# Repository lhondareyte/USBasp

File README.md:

## USBasp firmware
Latest version of USBasp firmware with TPI support and Green Photon hack for chinese ISP programmers based on ATmega8/48/88.

See [Thomas Fischl's website](https://www.fischl.de/usbasp/) and [Green Photons's blog](https://www.sciencetronics.com/greenphotons/?p=1937) for details.

### Build
Make sure you have avr-gcc toolchain installed. To build the patched version, just type:

`make main.hex`

To build original version, just type:

`make -f Makefile.genuine main.hex`

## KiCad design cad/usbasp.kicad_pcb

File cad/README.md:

## USBasp schematics with 3v3 support

* [See here for details](http://lhondareyte.free.fr/wordpress/?p=2791).
* [Thomas Fischl's original schematic](https://www.fischl.de/usbasp/).

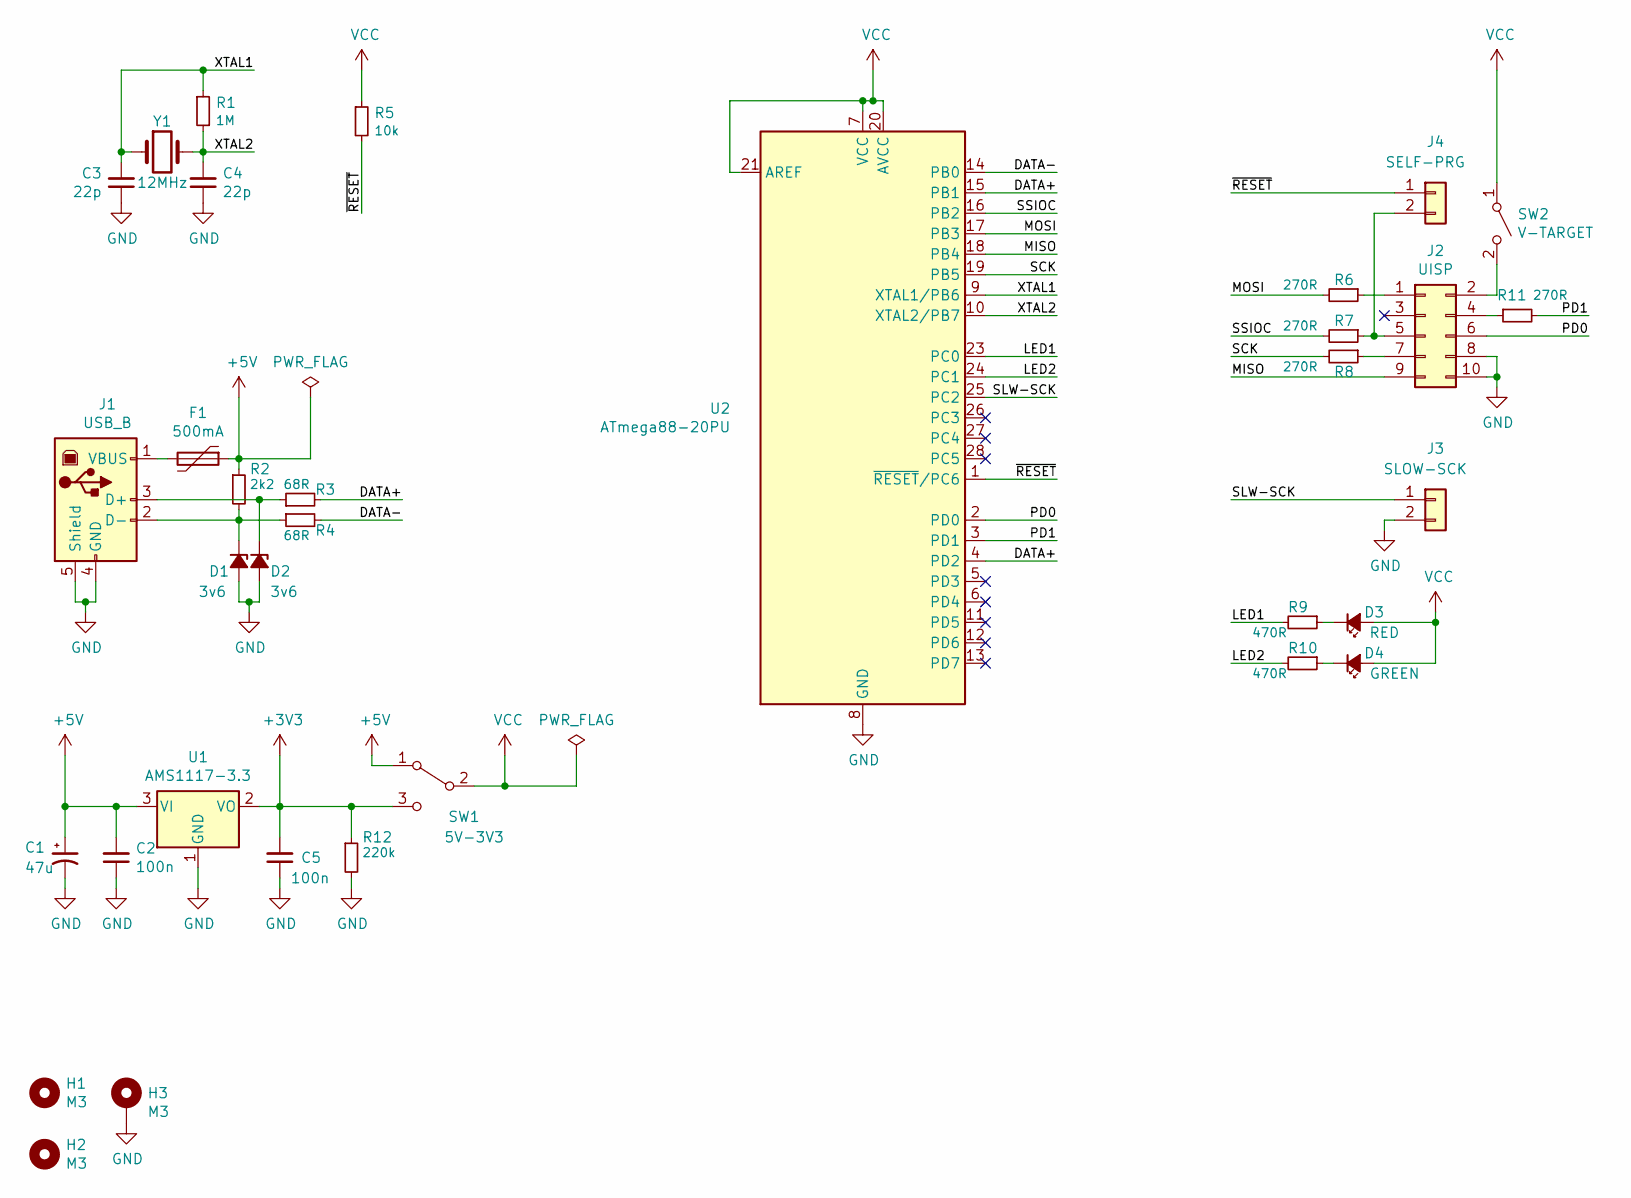
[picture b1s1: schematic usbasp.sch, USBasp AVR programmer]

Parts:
C1: 47u; CP_Radial_D5.0mm_P2.50mm
C2, C5: 100n; C_1206_3216Metric_Pad1.42x1.75mm_HandSolder
C3, C4: 22p; C_1206_3216Metric_Pad1.42x1.75mm_HandSolder
D1, D2: 3v6; D_1206_3216Metric_Pad1.42x1.75mm_HandSolder
D3: RED; LED_D3.0mm_FlatTop
D4: GREEN; LED_D3.0mm_FlatTop
F1: 500mA; D_1206_3216Metric_Pad1.42x1.75mm_HandSolder
H1, H2: M3; MountingHole_3.2mm_M3
H3: M3; MountingHole_3.2mm_M3_Pad
J1: USB_B; USB_B_OST_USB-B1HSxx_Horizontal
J2: UISP; PinHeader_2x05_P2.54mm_Horizontal
J3: SLOW-SCK; PinHeader_1x02_P2.54mm_Vertical
J4: SELF-PRG; PinHeader_1x02_P2.54mm_Vertical
R1: 1M; R_1206_3216Metric_Pad1.42x1.75mm_HandSolder
R2: 2k2; R_1206_3216Metric_Pad1.42x1.75mm_HandSolder
R3, R4: 68R; R_1206_3216Metric_Pad1.42x1.75mm_HandSolder
R5: 10k; R_1206_3216Metric_Pad1.42x1.75mm_HandSolder
R6, R7, R8, R11: 270R; R_1206_3216Metric_Pad1.42x1.75mm_HandSolder
R9, R10: 470R; R_1206_3216Metric_Pad1.42x1.75mm_HandSolder
R12: 220k; R_1206_3216Metric_Pad1.42x1.75mm_HandSolder
SW1: 5V-3V3; PinHeader_1x03_P2.54mm_Vertical
SW2: V-TARGET; PinHeader_1x02_P2.54mm_Vertical
U1: AMS1117-3.3; SOT-223-3_TabPin2
U2: ATmega88-20PU; DIP-28_W7.62mm
Y1: 12MHz; Crystal_HC49-4H_Vertical

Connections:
+3V3: C5.2, R12.1, SW1.3 (C), U1.2 (VO)
+5V: C1.1, C2.2, F1.1, R2.1, SW1.1 (A), U1.3 (VI)
/DATA+: R3.2, U2.4 (PD2), U2.15 (PB1)
/DATA-: R4.2, U2.14 (PB0)
/LED1: R9.2, U2.23 (PC0)
/LED2: R10.2, U2.24 (PC1)
/MISO: J2.9, U2.18 (PB4)
/MOSI: R6.2, U2.17 (PB3)
/PD0: J2.6, U2.2 (PD0)
/PD1: R11.2, U2.3 (PD1)
/SCK: R8.2, U2.19 (PB5)
/SLW-SCK: J3.1, U2.25 (PC2)
/SSIOC: R7.2, U2.16 (PB2)
/XTAL1: C3.2, R1.1, U2.9 (XTAL1/PB6), Y1.1
/XTAL2: C4.2, R1.2, U2.10 (XTAL2/PB7), Y1.2
/~RESET: J4.1, R5.2, U2.1 (~RESET~/PC6)
GND: C1.2, C2.1, C3.1, C4.1, C5.1, D1.2 (A), D2.2 (A), H3.1, J1.4 (GND), J1.5 (Shield), J2.8, J2.10, J3.2, R12.2, U1.1 (GND), U2.8 (GND), U2.22 (GND)
unnamed: D1.1 (K), J1.2 (D-), R2.2, R4.1
unnamed: D2.1 (K), J1.3 (D+), R3.1
unnamed: D3.1 (K), R9.1
unnamed: D4.1 (K), R10.1
unnamed: F1.2, J1.1 (VBUS)
unnamed: J2.1, R6.1
unnamed: J2.2, SW2.2 (B)
unnamed: J2.4, R11.1
unnamed: J2.5, J4.2, R7.1
unnamed: J2.7, R8.1
VCC: D3.2 (A), D4.2 (A), R5.1, SW1.2 (B), SW2.1 (A), U2.7 (VCC), U2.20 (AVCC), U2.21 (AREF)

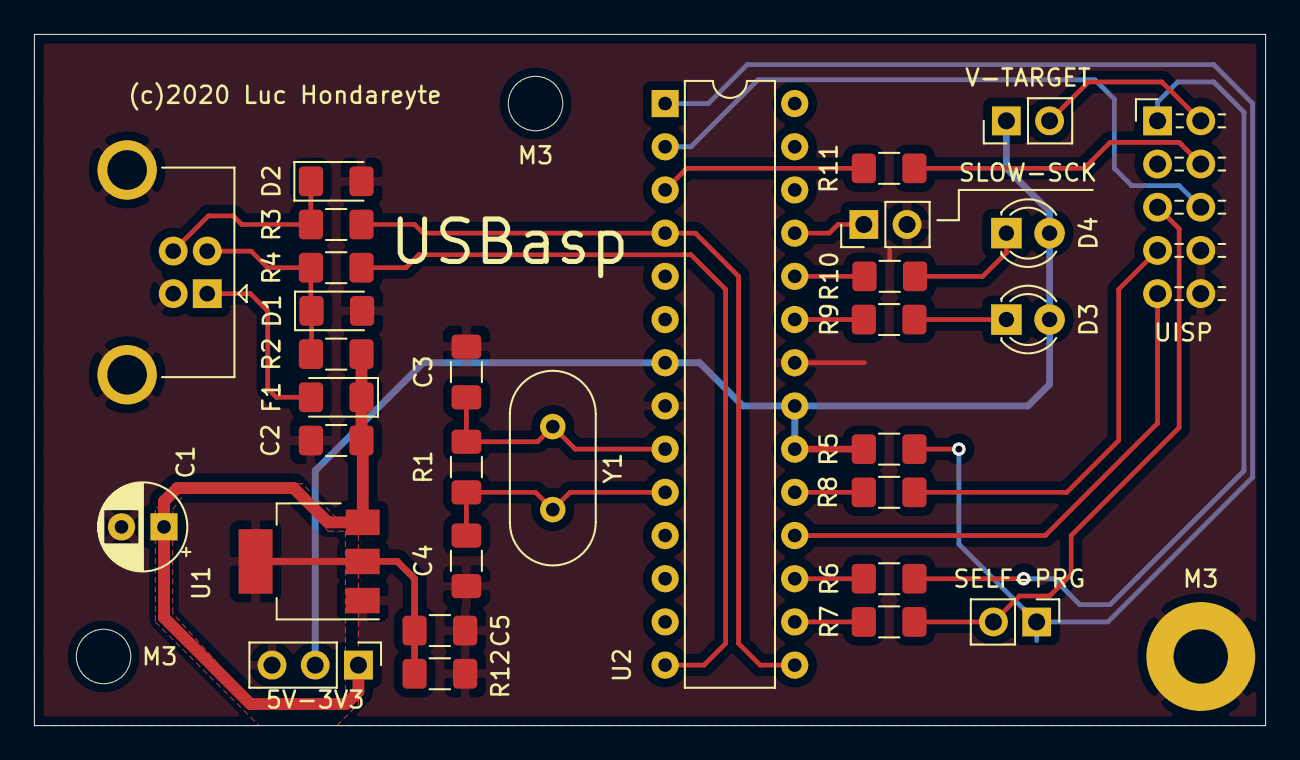
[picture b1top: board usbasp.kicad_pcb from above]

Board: 2 copper layers, 72.4 x 40.6 mm, 34 parts (0 on the bottom side), 28 nets.

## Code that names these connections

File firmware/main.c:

/*
 * USBasp - USB in-circuit programmer for Atmel AVR controllers
 *
 * Thomas Fischl <tfischl@gmx.de>
 *
 * License........: GNU GPL v2 (see Readme.txt)
 * Target.........: ATMega8 at 12 MHz
 * Creation Date..: 2005-02-20
 * Last change....: 2009-02-28
 *
 * PC2 SCK speed option.
 * GND  -> slow (8khz SCK),
 * open -> software set speed (default is 375kHz SCK)
 */

#include <avr/io.h>
#include <avr/interrupt.h>
#include <avr/pgmspace.h>
#include <avr/wdt.h>

#include "usbasp.h"
#include "usbdrv.h"
#include "isp.h"
#include "clock.h"
#include "tpi.h"
#include "tpi_defs.h"

static uchar replyBuffer[8];

static uchar prog_state = PROG_STATE_IDLE;
static uchar prog_sck = USBASP_ISP_SCK_AUTO;

static uchar prog_address_newmode = 0;
static unsigned long prog_address;
static unsigned int prog_nbytes = 0;
static unsigned int prog_pagesize;
static uchar prog_blockflags;
static uchar prog_pagecounter;

uchar usbFunctionSetup(uchar data[8]) {

	uchar len = 0;

	if (data[1] == USBASP_FUNC_CONNECT) {

		/* set SCK speed */
		if ((PINC & (1 << PC2)) == 0) {
			ispSetSCKOption(USBASP_ISP_SCK_8);
		} else {
			ispSetSCKOption(prog_sck);
		}

		/* set compatibility mode of address delivering */
		prog_address_newmode = 0;

		ledRedOn();
		ispConnect();

	} else if (data[1] == USBASP_FUNC_DISCONNECT) {
		ispDisconnect();
		ledRedOff();

	} else if (data[1] == USBASP_FUNC_TRANSMIT) {
		replyBuffer[0] = ispTransmit(data[2]);
		replyBuffer[1] = ispTransmit(data[3]);
		replyBuffer[2] = ispTransmit(data[4]);
		replyBuffer[3] = ispTransmit(data[5]);
		len = 4;

	} else if (data[1] == USBASP_FUNC_READFLASH) {

		if (!prog_address_newmode)
			prog_address = (data[3] << 8) | data[2];

		prog_nbytes = (data[7] << 8) | data[6];
		prog_state = PROG_STATE_READFLASH;
		len = 0xff; /* multiple in */

	} else if (data[1] == USBASP_FUNC_READEEPROM) {

		if (!prog_address_newmode)
			prog_address = (data[3] << 8) | data[2];

		prog_nbytes = (data[7] << 8) | data[6];
		prog_state = PROG_STATE_READEEPROM;
		len = 0xff; /* multiple in */

	} else if (data[1] == USBASP_FUNC_ENABLEPROG) {
		replyBuffer[0] = ispEnterProgrammingMode();
		len = 1;

	} else if (data[1] == USBASP_FUNC_WRITEFLASH) {

		if (!prog_address_newmode)
			prog_address = (data[3] << 8) | data[2];

		prog_pagesize = data[4];
		prog_blockflags = data[5] & 0x0F;
		prog_pagesize += (((unsigned int) data[5] & 0xF0) << 4);
		if (prog_blockflags & PROG_BLOCKFLAG_FIRST) {
			prog_pagecounter = prog_pagesize;
		}
		prog_nbytes = (data[7] << 8) | data[6];
		prog_state = PROG_STATE_WRITEFLASH;
		len = 0xff; /* multiple out */

	} else if (data[1] == USBASP_FUNC_WRITEEEPROM) {

		if (!prog_address_newmode)
			prog_address = (data[3] << 8) | data[2];

		prog_pagesize = 0;
		prog_blockflags = 0;
		prog_nbytes = (data[7] << 8) | data[6];
		prog_state = PROG_STATE_WRITEEEPROM;
		len = 0xff; /* multiple out */

	} else if (data[1] == USBASP_FUNC_SETLONGADDRESS) {

		/* set new mode of address delivering (ignore address delivered in commands) */
		prog_address_newmode = 1;
		/* set new address */
		prog_address = *((unsigned long*) &data[2]);

	} else if (data[1] == USBASP_FUNC_SETISPSCK) {

		/* set sck option */
		prog_sck = data[2];
		replyBuffer[0] = 0;
		len = 1;

	} else if (data[1] == USBASP_FUNC_TPI_CONNECT) {
		tpi_dly_cnt = data[2] | (data[3] << 8);

		/* RST high */
		ISP_OUT |= (1 << ISP_RST);
		ISP_DDR |= (1 << ISP_RST);

		clockWait(3);

		/* RST low */
		ISP_OUT &= ~(1 << ISP_RST);
		ledRedOn();

		clockWait(16);
		tpi_init();
	
	} else if (data[1] == USBASP_FUNC_TPI_DISCONNECT) {

		tpi_send_byte(TPI_OP_SSTCS(TPISR));
		tpi_send_byte(0);

		clockWait(10);

		/* pulse RST */
		ISP_OUT |= (1 << ISP_RST);
		clockWait(5);
		ISP_OUT &= ~(1 << ISP_RST);
		clockWait(5);

		/* set all ISP pins inputs */
		ISP_DDR &= ~((1 << ISP_RST) | (1 << ISP_SCK) | (1 << ISP_MOSI));
		/* switch pullups off */
		ISP_OUT &= ~((1 << ISP_RST) | (1 << ISP_SCK) | (1 << ISP_MOSI));

		ledRedOff();
	
	} else if (data[1] == USBASP_FUNC_TPI_RAWREAD) {
		replyBuffer[0] = tpi_recv_byte();
		len = 1;
	
	} else if (data[1] == USBASP_FUNC_TPI_RAWWRITE) {
		tpi_send_byte(data[2]);
	
	} else if (data[1] == USBASP_FUNC_TPI_READBLOCK) {
		prog_address = (data[3] << 8) | data[2];
		prog_nbytes = (data[7] << 8) | data[6];
		prog_state = PROG_STATE_TPI_READ;
		len = 0xff; /* multiple in */
	
	} else if (data[1] == USBASP_FUNC_TPI_WRITEBLOCK) {
		prog_address = (data[3] << 8) | data[2];
		prog_nbytes = (data[7] << 8) | data[6];
		prog_state = PROG_STATE_TPI_WRITE;
		len = 0xff; /* multiple out */
	
	} else if (data[1] == USBASP_FUNC_GETCAPABILITIES) {
		replyBuffer[0] = USBASP_CAP_0_TPI;
		replyBuffer[1] = 0;
		replyBuffer[2] = 0;
		replyBuffer[3] = 0;
		len = 4;
	}

	usbMsgPtr = replyBuffer;

	return len;
}

uchar usbFunctionRead(uchar *data, uchar len) {

	uchar i;

	/* check if programmer is in correct read state */
	if ((prog_state != PROG_STATE_READFLASH) && (prog_state
			!= PROG_STATE_READEEPROM) && (prog_state != PROG_STATE_TPI_READ)) {
		return 0xff;
	}

	/* fill packet TPI mode */
	if(prog_state == PROG_STATE_TPI_READ)
	{
		tpi_read_block(prog_address, data, len);
		prog_address += len;
		return len;
	}

	/* fill packet ISP mode */
	for (i = 0; i < len; i++) {
		if (prog_state == PROG_STATE_READFLASH) {
			data[i] = ispReadFlash(prog_address);
		} else {
			data[i] = ispReadEEPROM(prog_address);
		}
		prog_address++;
	}

	/* last packet? */
	if (len < 8) {
		prog_state = PROG_STATE_IDLE;
	}

	return len;
}

uchar usbFunctionWrite(uchar *data, uchar len) {

	uchar retVal = 0;
	uchar i;

	/* check if programmer is in correct write state */
	if ((prog_state != PROG_STATE_WRITEFLASH) && (prog_state
			!= PROG_STATE_WRITEEEPROM) && (prog_state != PROG_STATE_TPI_WRITE)) {
		return 0xff;
	}

	if (prog_state == PROG_STATE_TPI_WRITE)
	{
		tpi_write_block(prog_address, data, len);
		prog_address += len;
		prog_nbytes -= len;
		if(prog_nbytes <= 0)
		{
			prog_state = PROG_STATE_IDLE;
			return 1;
		}
		return 0;
	}

	for (i = 0; i < len; i++) {

		if (prog_state == PROG_STATE_WRITEFLASH) {
			/* Flash */

			if (prog_pagesize == 0) {
				/* not paged */
				ispWriteFlash(prog_address, data[i], 1);
			} else {
				/* paged */
				ispWriteFlash(prog_address, data[i], 0);
				prog_pagecounter--;
				if (prog_pagecounter == 0) {
					ispFlushPage(prog_address, data[i]);
					prog_pagecounter = prog_pagesize;
				}
			}

		} else {
			/* EEPROM */
			ispWriteEEPROM(prog_address, data[i]);
		}

		prog_nbytes--;

		if (prog_nbytes == 0) {
			prog_state = PROG_STATE_IDLE;
			if ((prog_blockflags & PROG_BLOCKFLAG_LAST) && (prog_pagecounter
					!= prog_pagesize)) {

				/* last block and page flush pending, so flush it now */
				ispFlushPage(prog_address, data[i]);
			}

			retVal = 1; // Need to return 1 when no more data is to be received
		}

		prog_address++;
	}

	return retVal;
}

int main(void) {
	uchar i, j;

	/* no pullups on USB and ISP pins */
	PORTD = 0;
	PORTB = 0;
#if defined (__GREEN_PHOTONS__)
	DDRD = 0x00;
#else
	/* all outputs except PD2 = INT0 */
	DDRD = ~(1 << 2);
#endif

	/* output SE0 for USB reset */
	DDRB = ~0;
	j = 0;
	/* USB Reset by device only required on Watchdog Reset */
	while (--j) {
		i = 0;
		/* delay >10ms for USB reset */
		while (--i)
			;
	}
	/* all USB and ISP pins inputs */
	DDRB = 0;

	/* all inputs except PC0, PC1 */
	DDRC = 0x03;
	PORTC = 0xfe;

	/* init timer */
	clockInit();

	/* main event loop */
	usbInit();
	sei();
	for (;;) {
		usbPoll();
	}
	return 0;
}

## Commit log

2018-02-11 Initial import.
2018-02-11 Add Green Photons workaround.
2018-02-11 Update README.md.
2020-05-09 Adding KiCad schematic.
2020-05-28 Schematic: add 3.3v support
2020-06-21 Add Makefile for genuine version
2020-06-27 cad: update USB connector 3D model.
2021-03-17 Update permissions

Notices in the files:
cad/usbasp.kicad_pcb:
(c)2020 Luc Hondareyte
